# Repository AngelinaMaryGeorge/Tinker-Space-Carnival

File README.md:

# Badge Name: Red-blue

> Space Carnival 2026 — PCB Badge Design Competition entry.
> Competition guide: https://space-carnival-psi.vercel.app/badge/

**Designer(s):** Angelina Mary George, Kochi, and a github.com/AngelinaMaryGeorge

## The idea

A compact 40 × 40 mm USB-A powered badge that alternates a Blue and Red LED using a classic NE555P timer, while doubling as a pocket millimeter ruler along its edge for everyday desk use.

## Theme

It celebrates Kochi and Kerala's resourceful, hands-on maker culture by turning a classic analog circuit into a practical keepsake tool built for tinkering at TinkerSpace.

## How it works

- **Power:** 5 V USB (horizontal male USB-A plug)
- **Main parts:** 1 × NE555P timer IC (DIP-8), 2 × 5 mm LEDs (Blue & Red), 4 × through-hole resistors (2 × 330 Ω, 1 × 1 kΩ, 1 × 150 kΩ), 2 × capacitors (10 µF, 10 nF), 1 × USB-A male plug
- **What happens when you power it:** Plugging it into any USB-A port, laptop, or power bank runs the NE555P in astable mode, causing the Blue and Red LEDs to blink alternately.

## Soldering experience

To solder: 9 easy through-hole components and 1 wide-pitch USB-A plug in about 15–20 minutes.

## Checklist

- [x] Board fits within 40 × 40 mm
- [x] Total BOM under ₹50 per badge, including the PCB and battery (see `bom.csv`)
- [x] Every BOM row has quantity, unit price at 300 units and a source link
- [x] Manufacturable by Lion Circuits (checked against their capabilities)
- [x] Schematic in `schematic/` (PDF + source files)
- [x] Gerbers zipped in `gerber/`
- [x] Render or photo(s) in `images/`

**BOM total per badge:** ₹34.39 (300 badge order)

## Files

| Folder / file | What goes in it |
| --- | --- |
| `schematic/` | KiCad schematic PDF (`Carnival.pdf`) and source files (`Carnival.kicad_sch`, `Carnival.kicad_pcb`) |
| `gerber/` | Zipped Gerber and Excellon drill files ready for Lion Circuits |
| `bom.csv` | Component list with quantities, 300-unit prices (₹), and source links |
| `images/` | 3D front and back renders of the badge (plus Lion Circuits quote screenshot) |

## License

MIT License (see `LICENSE` file).

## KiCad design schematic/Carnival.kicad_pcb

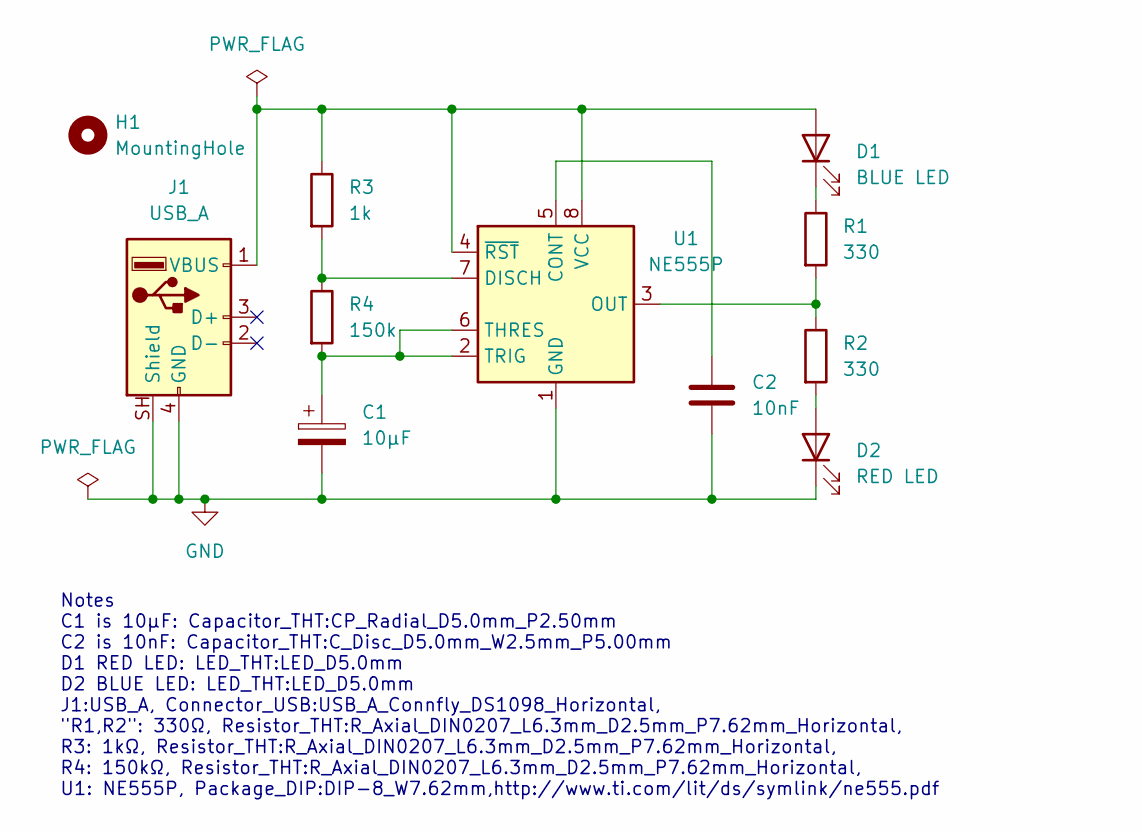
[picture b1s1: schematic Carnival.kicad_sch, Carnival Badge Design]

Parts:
C1: 10µF; CP_Radial_D5.0mm_P2.50mm
C2: 10nF; C_Disc_D5.0mm_W2.5mm_P5.00mm
D1: BLUE LED; LED_D5.0mm
D2: RED LED; LED_D5.0mm
H1: MountingHole; MountingHole_3mm
J1: USB_A; USB_A_Connfly_DS1098_Horizontal
R1, R2: 330; R_Axial_DIN0207_L6.3mm_D2.5mm_P7.62mm_Horizontal
R3: 1k; R_Axial_DIN0207_L6.3mm_D2.5mm_P7.62mm_Horizontal
R4: 150k; R_Axial_DIN0207_L6.3mm_D2.5mm_P7.62mm_Horizontal
U1: NE555P; DIP-8_W7.62mm

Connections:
GND: C1.2, C2.2, D2.1 (K), J1.4 (GND), J1.SH (Shield), U1.1 (GND)
unnamed: D1.2 (A), J1.1 (VBUS), R3.1, U1.4 (~RST), U1.8 (VCC)
unnamed: D1.1 (K), R1.1
unnamed: D2.2 (A), R2.2
unnamed: C2.1, U1.5 (CONT)
unnamed: R3.2, R4.1, U1.7 (DISCH)
unnamed: R1.2, R2.1, U1.3 (OUT)
unnamed: C1.1, R4.2, U1.2 (TRIG), U1.6 (THRES)

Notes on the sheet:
Notes C1 is 10µF: Capacitor_THT:CP_Radial_D5.0mm_P2.50mm C2 is 10nF: Capacitor_THT:C_Disc_D5.0mm_W2.5mm_P5.00mm D1 RED LED: LED_THT:LED_D5.0mm D2 BLUE LED: LED_THT:LED_D5.0mm J1:USB_A, Connector_USB:USB_A_Connfly_DS1098_Horizontal, "R1,R2": 330Ω, Resistor_THT:R_Axial_DIN0207_L6.3mm_D2.5mm_P7.62mm_H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

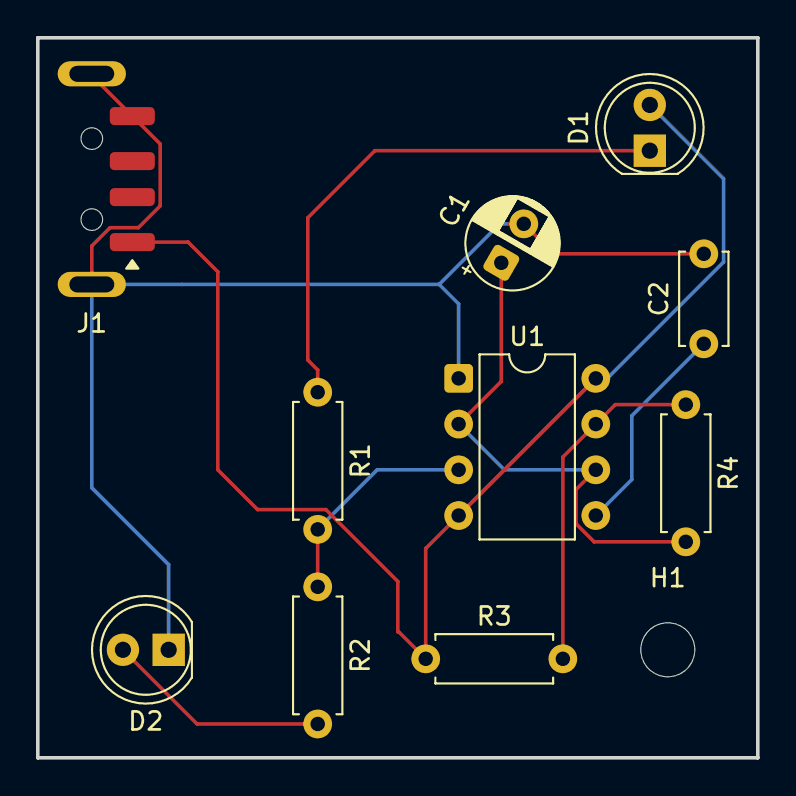
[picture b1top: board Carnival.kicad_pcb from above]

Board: 2 copper layers, 40.0 x 40.0 mm, 11 parts (0 on the bottom side), 8 nets.

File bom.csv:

Reference,Qty,Value,DNP,Exclude from BOM,Exclude from Board,Exclude from Simulation,Exclude from Position Files,Footprint,Datasheet
C1,1,10µF,,,,,${EXCLUDE_FROM_POS_FILES},Capacitor_THT:CP_Radial_D5.0mm_P2.50mm,
C2,1,10nF,,,,,${EXCLUDE_FROM_POS_FILES},Capacitor_THT:C_Disc_D5.0mm_W2.5mm_P5.00mm,
D1,1,BLUE,,,,,${EXCLUDE_FROM_POS_FILES},LED_THT:LED_D5.0mm,
D2,1,RED,,,,,${EXCLUDE_FROM_POS_FILES},LED_THT:LED_D5.0mm,
J1,1,USB_A,,,,,${EXCLUDE_FROM_POS_FILES},Connector_USB:USB_A_Connfly_DS1098_Horizontal,
"R1,R2",2,330Ω,,,,,${EXCLUDE_FROM_POS_FILES},Resistor_THT:R_Axial_DIN0207_L6.3mm_D2.5mm_P7.62mm_Horizontal,
R3,1,1kΩ,,,,,${EXCLUDE_FROM_POS_FILES},Resistor_THT:R_Axial_DIN0207_L6.3mm_D2.5mm_P7.62mm_Horizontal,
R4,1,150kΩ,,,,,${EXCLUDE_FROM_POS_FILES},Resistor_THT:R_Axial_DIN0207_L6.3mm_D2.5mm_P7.62mm_Horizontal,
U1,1,NE555P,,,,,${EXCLUDE_FROM_POS_FILES},Package_DIP:DIP-8_W7.62mm,http://www.ti.com/lit/ds/symlink/ne555.pdf
